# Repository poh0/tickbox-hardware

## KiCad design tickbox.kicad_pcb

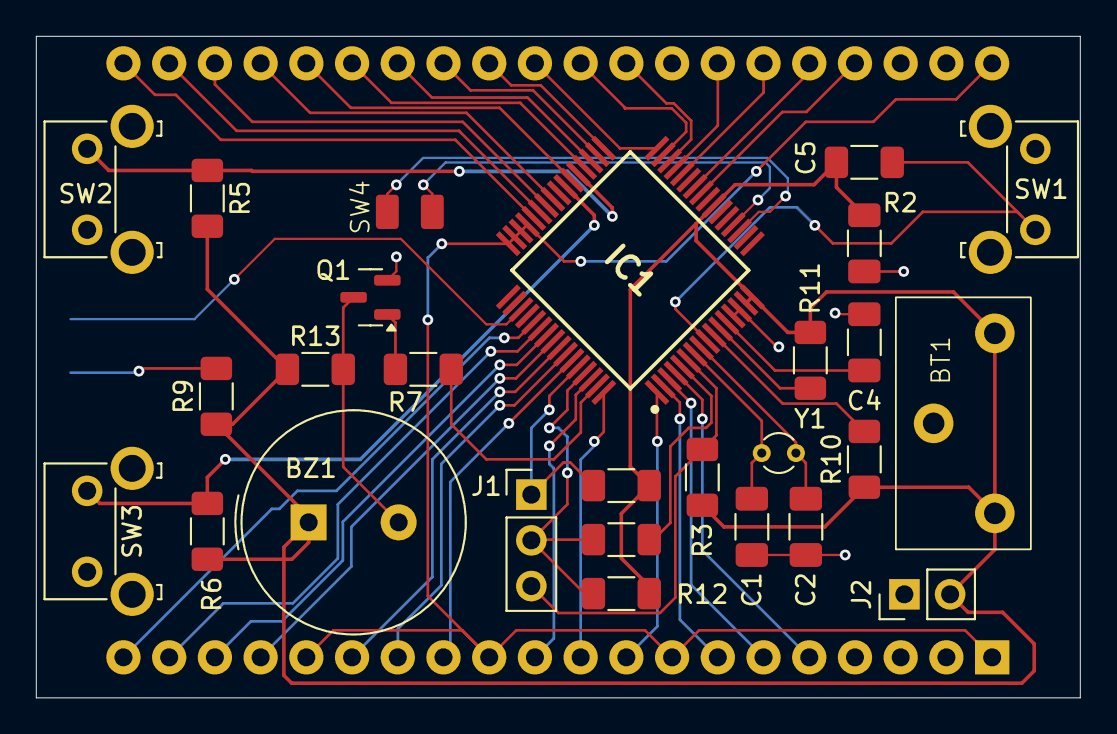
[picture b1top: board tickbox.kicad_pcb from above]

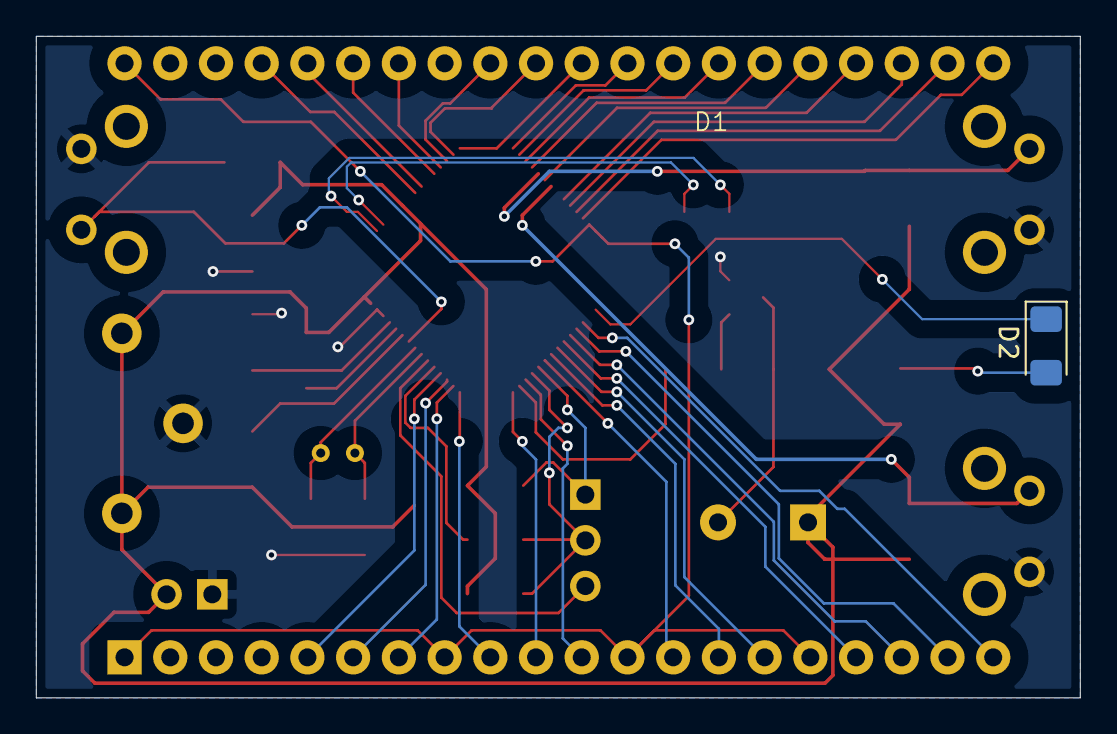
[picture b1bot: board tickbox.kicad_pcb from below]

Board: 4 copper layers, 58.0 x 36.8 mm, 29 parts (2 on the bottom side), 51 nets.

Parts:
BT1: Battery_Cell; COIN_HOLDER_TH
BZ1: Buzzer; Buzzer_TDK_PS1240P02BT_D12.2mm_H6.5mm
C1, C2: 8pf; C_1206_3216Metric_Pad1.33x1.80mm_HandSolder
C4: 0.47uF; C_1206_3216Metric_Pad1.33x1.80mm_HandSolder
C5: 0.1uF; C_1206_3216Metric_Pad1.33x1.80mm_HandSolder
D1: VI-402
D2: LED; LED_1206_3216Metric_Pad1.42x1.75mm_HandSolder
IC1: R5F10RLAGFB#10; QFP50P1200X1200X170-64M
J1: Conn_01x03_Pin; PinHeader_1x03_P2.54mm_Vertical
J2: Conn_01x02_Pin; PinHeader_1x02_P2.54mm_Vertical
Q1: BC848; SOT-23
R1, R2, R5, R6, R10, R11, R12: 10k; R_1206_3216Metric_Pad1.30x1.75mm_HandSolder
R3, R13: 1k; R_1206_3216Metric_Pad1.30x1.75mm_HandSolder
R4: 2k; R_1206_3216Metric_Pad1.30x1.75mm_HandSolder
R7: 4.7k; R_1206_3216Metric_Pad1.30x1.75mm_HandSolder
R9: 1.6k; R_1206_3216Metric_Pad1.30x1.75mm_HandSolder
SW1, SW2, SW3: SW_MEC_5G; SW_SPST_Omron_B3F-315x_Angled
SW4: SW_MEC_5G; Wire_pads
Y1: 32.768 kHz; Crystal_DS26_D2.0mm_L6.0mm_Vertical

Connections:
/COM: D1.1 (COM), D1.8 (DP1), D1.12 (DP2), D1.16 (DP3), D1.40 (COM), IC1.45 (COM3), IC1.46 (COM2), IC1.47 (COM1), IC1.48 (COM0)
/PCLBUZ0: IC1.63 (P140/TO00/PCLBUZ0/SEG27/(INTP6)), R7.1
/RESET: IC1.6 (~RESET), J1.3, R3.2
/SEG0: D1.21 (4A), IC1.44 (COM4/SEG0)
/SEG1: D1.22 (4F), IC1.43 (COM5/SEG1)
/SEG2: D1.23 (4G), IC1.42 (COM6/SEG2)
/SEG3: D1.24 (3B), IC1.41 (COM7/SEG3)
/SEG6: D1.25 (3A), IC1.38 (P17/SO01/TI02/TO02/SEG6)
/SEG8: D1.26 (3F), IC1.36 (P51/TI06/TO06/SEG8)
/SEG9: D1.27 (3G), IC1.35 (P52/INTP6/SEG9)
/SEG10: D1.28 (COL), IC1.34 (P53/TI07/TO07/SEG10/(INTP1))
/SEG11: D1.29 (2B), IC1.33 (P54/SEG11/(TI02)/(TO02)/(INTP2))
/SEG12: D1.30 (2A), IC1.32 (P74/SEG12)
/SEG13: D1.31 (2F), IC1.31 (P73/KR3/SEG13)
/SEG14: D1.32 (2G), IC1.30 (P72/KR2/SEG14)
/SEG15: D1.34 (1B), IC1.29 (P71/KR1/SEG15)
/SEG16: D1.35 (1A), IC1.28 (P70/KR0/SEG16)
/SEG18: D1.36 (1F), IC1.26 (P31/INTP3/RTC1HZ/SEG18)
/SEG19: D1.37 (1G), IC1.25 (P30/TI01/TO01/SEG19)
/SEG22: D1.5 (1E), IC1.4 (P43/INTP7/SEG22)
/SEG23: D1.6 (1D), IC1.3 (P42/TI05/TO05/SEG23)
/SEG24: D1.7 (1C), IC1.2 (P41/ANI16/TI04/TO04/SEG24)
/SEG25: D1.9 (2E), IC1.1 (P120/ANI17/SEG25)
/SEG26: D1.10 (2D), IC1.64 (P141/TI00/PCLBUZ1/SEG26/(INTP7))
/SEG28: D1.11 (2C), IC1.62 (P10/~SCK00/SEG28)
/SEG31: D1.13 (3E), IC1.59 (P13/ANI18/SEG31)
/SEG32: D1.14 (3D), IC1.58 (P14/ANI19/SEG32)
/SEG33: D1.15 (3C), IC1.57 (P142/ANI20/SEG33)
/SEG34: D1.17 (4E), IC1.56 (P143/ANI21/SEG34)
/SEG35: D1.18 (4D), IC1.55 (P144/ANI22/SEG35)
/SEG36: D1.19 (4C), IC1.54 (P145/ANI23/SEG36)
/SEG37: D1.20 (4B), IC1.53 (P146/SEG37)
/SWIN: IC1.19 (P127/CAPH), SW4.3 (B)
/SWOUT: IC1.20 (P126/CAPL), SW4.1 (A)
/TOOL0: IC1.5 (P40/TOOL0), R4.1
/TOOLRXD: IC1.61 (P11/SI00/RXD0/TOOLRXD/SEG29), J1.2, R4.2, R12.2
/TOOLTXD: IC1.60 (P12/SO00/TXD0/TOOLTXD/SEG30), J1.1, R1.2
/XT1: C2.2, IC1.8 (P123/XT1), Y1.1
/XT2: C1.2, IC1.7 (P124/XT2/EXCLKS), Y1.2
GND: BT1.2 (-), C1.1, C2.1, C4.2, C5.2, IC1.13 (VSS), IC1.14 (EVSS), J2.1, Q1.2 (E), SW1.1 (A), SW2.1 (A), SW3.1 (A)
unnamed: BZ1.2 (-), Q1.3 (C), R13.2
unnamed: D2.2 (A), R9.2
unnamed: D2.1 (K), IC1.51 (P130)
unnamed: IC1.39 (P16/SI01/INTP2/SEG5), R6.1, SW3.3 (B)
unnamed: IC1.37 (P50/INTP5/SEG7/(PCLBUZ0)), R5.1, SW2.3 (B)
unnamed: IC1.11 (P121/X1), R11.2
unnamed: IC1.10 (P122/X2/EXCLK), R10.2
unnamed: IC1.9 (P137/INTP0), R2.1, SW1.3 (B)
unnamed: C4.1, IC1.12 (REGC)
unnamed: Q1.1 (B), R7.2
VDD: BT1.1 (+), BZ1.1 (+), C5.1, IC1.15 (VDD), IC1.16 (EVDD), IC1.23 (VL4), J2.2, R1.1, R2.2, R3.1, R5.2, R6.2, R9.1, R10.1, R11.1, R12.1, R13.1

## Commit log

2025-06-30 Added custom symbols, started drawing schematic
2025-07-01 add rpi programming header
2025-07-11 Added LCD pads footprint
2025-07-18 Assing footprints + slight changes to schematic
2025-07-21 added alarm switch
2025-07-30 Sketch PCB layout
2025-09-14 add coin holder etc
